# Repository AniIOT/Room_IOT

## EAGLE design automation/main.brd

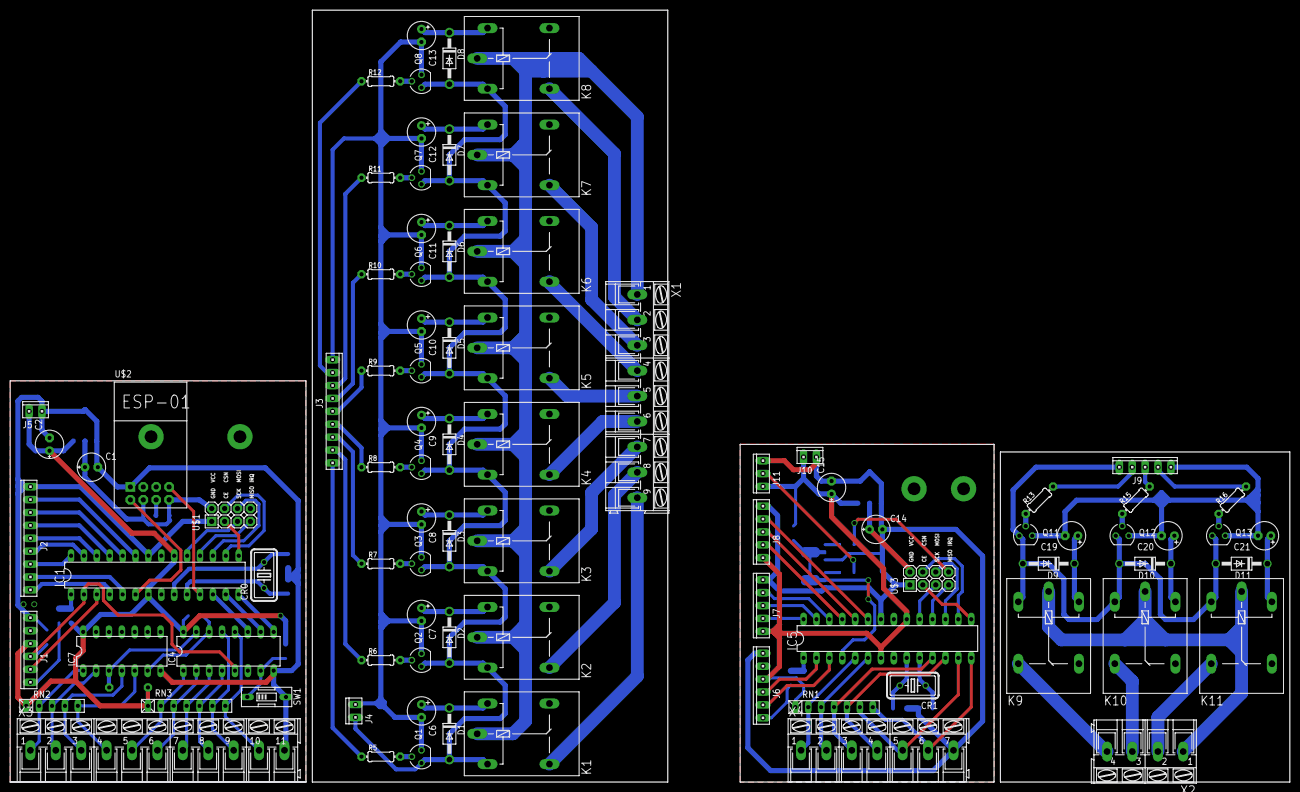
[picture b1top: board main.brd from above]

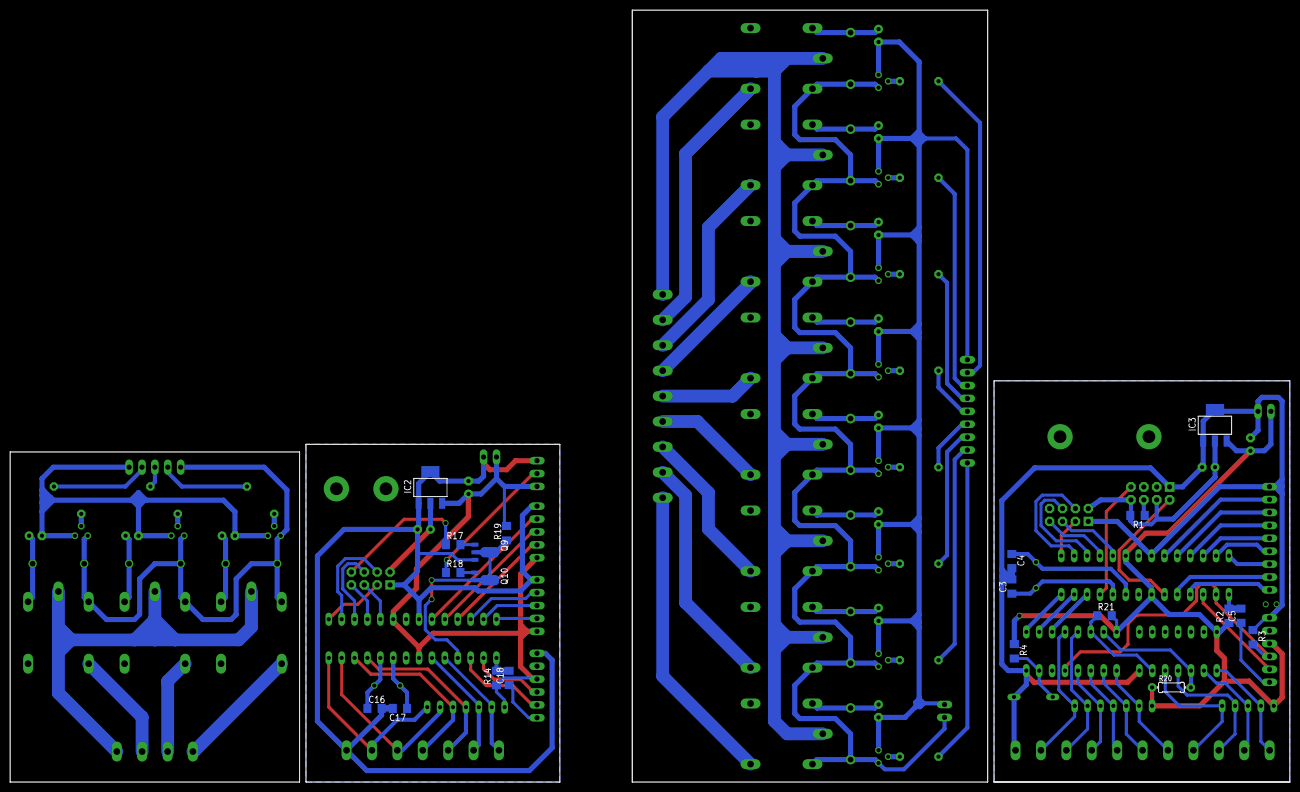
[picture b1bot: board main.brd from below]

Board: 2 copper layers, 252.0 x 152.0 mm, 107 parts (20 on the bottom side), 122 nets.

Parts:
C1, C2: E2,5-6E
C3, C4, C5, C16, C17: C1206
C6, C7, C8, C9, C10, C11, C12, C13, C19, C20, C21: E2,5-6
C14: 100uF; E2,5-6E
C15: 10uF; E2,5-6E
C18: 100nF; C1206
CR0, CR1: 16MHz; HC18U-V
D1, D2, D3, D4, D5, D6, D7, D8, D9, D10, D11: 1N4004; DO41-10
IC1, IC5: ATMEGA328-20P; DIL28-3
IC2, IC3: LM1117IMPX-3.3; SOT223
IC4: 74LS151N; DIL16
IC7: 74LS86N; DIL14
J1, J6: 10X06MTA
J2, J3: 10X09MTA
J4, J5, J10: 10X02MTA
J7, J8, J9: 10X05MTA
J11: 10X03MTA
K1, K2, K3, K4, K5, K6, K7, K8, K9, K10, K11: G5L; G5LE
Q1, Q2, Q3, Q4, Q5, Q6, Q7, Q8, Q11, Q12, Q13: BC547; SOT54A
Q9, Q10: SOT89-BCE
R1, R2, R3, R4, R14, R17, R18, R19, R21: R1206
R5, R6, R7, R8, R9, R10, R11, R12, R13, R15, R16, R20: 0204/7
RN1, RN3: RN-7
RN2: RN-5
SW1: EDG-01
U$1, U$3: NRF24L01+
U$2: ESP01
X1: AK300/9
X2: AK300/4
X3: AK300/11
X4: AK300/7

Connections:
3V3: C1.+, IC3.2, R1.2, U$1.VCC, U$2.CH_PD, U$2.VCC
3V3@2: C14.+, IC2.2, U$3.VCC
5V: C2.+, IC1.7, IC1.20, IC3.3, IC4.16, IC7.14, J1.3, J5.2, R2.1, R4.1, R20.1, R21.2, RN2.1, RN3.1
5V@1: D1.A, D2.A, D3.A, D4.A, D5.A, D6.A, D7.A, D8.A, J4.2, K1.1, K2.1, K3.1, K4.1, K5.1, K6.1, K7.1, K8.1, Q1.C, Q2.C, Q3.C, Q4.C, Q5.C, Q6.C, Q7.C, Q8.C
5V@2: C15.+, IC2.3, IC5.7, IC5.20, J6.3, J7.5, J8.5, J10.2, J11.3, R14.1, R19.2, RN1.1
5V@2R: D9.A, D10.A, D11.A, J9.5, K9.1, K10.1, K11.1, Q11.C, Q12.C, Q13.C
CE: IC1.15, U$1.CE
CE2: IC5.15, U$3.CE
CR1: C4.1, CR0.2, IC1.9
CR2: C3.1, CR0.1, IC1.10
CR3: C16.1, CR1.1, IC5.10
CR4: C17.1, CR1.2, IC5.9
CSN: IC1.16, U$1.CSN
CSN2: IC5.16, U$3.CSN
DTR: C5.1, J1.6
DTR2: C18.1, J6.6
ERST: R1.1, U$2.RST
FSW1: IC7.1, RN2.2, X3.1
FSW2: IC7.2, RN2.3, X3.2
GND: C1.-, C2.-, C3.2, C4.2, IC1.22, IC3.1, IC3.TAB, IC4.8, IC7.7, J1.1, J2.1, J5.1, R3.1, SW1.2, U$1.GND, U$2.GND, X3.11
GND@1: C6.-, C7.-, C8.-, C9.-, C10.-, C11.-, C12.-, C13.-, J3.9, J4.1, Q1.E, Q2.E, Q3.E, Q4.E, Q5.E, Q6.E, Q7.E, Q8.E
GND@2: C14.-, C15.-, C16.2, C17.2, IC2.1, IC2.TAB, IC5.22, J6.1, J7.1, J8.1, J10.1, J11.1, Q9.E, Q10.E, U$3.GND, X4.7
GND@2R: C19.-, C20.-, C21.-, J9.1, Q11.E, Q12.E, Q13.E
IRQ: R17.1, U$3.IRQ
IRQ+PIR: IC5.4, Q9.C, Q10.C, R19.1
LIVE: K1.P, K2.P, K3.P, K4.P, K5.P, K6.P, K7.P, K8.P, X1.1
MEN: IC4.7, R4.2, SW1.1
MISO: IC1.18, U$1.MISO
MISO2: IC5.18, U$3.MISO
MOSI: IC1.17, U$1.MOSI
MOSI2: IC5.17, U$3.MOSI
MRST: C5.2, IC1.1, R2.2
MRST1: C18.2, IC5.1, R14.2
unnamed: K9.P, K10.P, K11.P, X2.1
unnamed: Q1.B, R5.2
unnamed: Q2.B, R6.2
unnamed: Q3.B, R7.2
unnamed: Q4.B, R8.2
unnamed: Q5.B, R9.2
unnamed: Q6.B, R10.2
unnamed: Q7.B, R11.2
unnamed: Q8.B, R12.2
unnamed: J3.1, R5.1
unnamed: J3.8, R12.1
unnamed: J3.7, R11.1
unnamed: J3.6, R10.1
unnamed: J3.5, R9.1
unnamed: J3.4, R8.1
unnamed: J3.3, R7.1
unnamed: J3.2, R6.1
unnamed: K1.S, X1.9
unnamed: K8.S, X1.2
unnamed: K7.S, X1.3
unnamed: K6.S, X1.4
unnamed: K5.S, X1.5
unnamed: K4.S, X1.6
unnamed: K3.S, X1.7
unnamed: K2.S, X1.8
unnamed: C19.+, D9.C, K9.2
unnamed: C7.+, D2.C, K2.2
unnamed: C8.+, D3.C, K3.2
unnamed: C9.+, D4.C, K4.2
unnamed: C10.+, D5.C, K5.2
unnamed: C11.+, D6.C, K6.2
unnamed: C12.+, D7.C, K7.2
unnamed: C13.+, D8.C, K8.2
unnamed: C6.+, D1.C, K1.2
unnamed: K10.S, X2.3
unnamed: C20.+, D10.C, K10.2
unnamed: K9.S, X2.4
unnamed: C21.+, D11.C, K11.2
unnamed: K11.S, X2.2
unnamed: Q11.B, R13.1
unnamed: Q13.B, R16.1
unnamed: Q12.B, R15.1
unnamed: J9.3, R15.2
unnamed: J9.4, R13.2
unnamed: J9.2, R16.2
unnamed: Q9.B, R17.2
unnamed: Q10.B, R18.2
PIR: J11.2, R18.1
PRX: IC1.3, J1.5
PRX2: IC5.3, J6.5
PTX2: IC5.2, J6.4
PTX+SWS: IC1.2, IC4.5, J1.4, R3.2
RELAY1: IC1.4, J2.9
RELAY2: IC1.5, J2.8
RELAY3: IC1.28, J2.7
RELAY4: IC1.27, J2.6
RELAY5: IC1.26, J2.5
RELAY6: IC1.25, J2.4
RELAY7: IC1.24, J2.3
RELAY8: IC1.23, J2.2
RELAY21: IC5.28, J7.4
RELAY22: IC5.27, J7.3
RELAY23: IC5.26, J7.2
RELAY24: IC5.25, J8.4
RELAY25: IC5.24, J8.3
RELAY26: IC5.23, J8.2
RX: IC1.11, U$2.RX
S1: IC1.12, IC4.11
S2: IC1.13, IC4.10
S3: IC1.14, IC4.9
S21: IC5.5, RN1.2, X4.1
S22: IC5.6, RN1.3, X4.2
S23: IC5.11, RN1.4, X4.3
S24: IC5.12, RN1.5, X4.4
S25: IC5.13, RN1.6, X4.5
S26: IC5.14, RN1.7, X4.6
SCK: IC1.19, U$1.SCK
SCK2: IC5.19, U$3.SCK
SW1: IC4.15, IC7.3, R20.2
SW2: IC4.14, IC7.6, R21.1
SW3: IC4.1, RN3.2, X3.5
SW4: IC4.2, RN3.3, X3.6
SW5: IC4.3, RN3.4, X3.7
SW6: IC4.4, RN3.5, X3.8
SW7: IC4.13, RN3.6, X3.9
SW8: IC4.12, RN3.7, X3.10
TSW1: IC7.4, RN2.4, X3.3
TSW2: IC7.5, RN2.5, X3.4
TX: IC1.6, U$2.TX

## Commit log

2019-09-12 Deposited all previous files
2019-09-12 Added de-bouncing for switches and a temporary function call in the wifi_comm state in main state machine
2019-09-13 added reference modbus and uart files
2019-09-13 corrected a few issues
2019-09-13 made changes to debouncing in gpio.ino, created files for node01 and added the new structure and debouncing of switches to gpio.ino
2019-09-15 Changed library for software serial, now using neoswserial which now has an isr to handle reception
2019-09-15 Created files and structure for esp8266 MODBUS_Rx.ino & MODBUS_Tx.ino: added and tested interrupt based serial comm
2019-09-15 changed folder name of esp_mqtt to esp_main
2019-09-20 lot of changes in communication.
2019-09-20 added esp flash download tools
2019-09-25 added callback funtion in esp_main which has tremendously reduced number of dropped packages.
2019-09-25 flash_download_tool
2019-09-26 added send data function call to callback function
2019-09-27 completed uart communication and mqtt callback
2019-09-27 no idea
2019-09-28 lotsa stuff
2019-09-29 added wtchdog and rf comm
2019-09-30 SP college ppt
2019-10-14 added state in main state machine for storing data in eeprom
2019-10-15 re-upload
2019-10-27 removed the separate folder for room
2019-11-07 header name changed to node02
2019-11-15 1. In esp_main.ino added software watchdog 2. In gpio.ino interchanged pins of extra switch and w4 as the cause of wrong switching was a hardware short 3. In node01.ino commented wifi_comm() to avoid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
2020-04-08 swapped switches
2020-04-11 Created V3 of code and added esp state machine
2020-04-16 1. Removed all .h files except for node00.h 2. Wrote code for MQTT connect request
2020-04-18 1. code for subscribe 2. code for ping 3. completed mqtt state machine 4. added call of esp state machine from mqtt state machine
2020-04-19 Restructuring of Repository
2020-04-19 refactoring of code to make connectToServer and subscribe functions generic with added function parameters
2020-04-19 Added esp tools
2020-04-24 Subscription and data acquisition from all 25 topics completed
2020-04-24 Added switch buffer and logic
2020-04-26 1. Added reconnect logic 2. Cleaned up code 3. Added logic fro checking connection to safe time
2020-04-26 1. Added Timed function calling (a rudimentary non-preemptive scheduler) 2. Made file and function for switches
2020-04-26 added else condition for connect and subscribe states in mqtt state-machine
2020-04-28 1. Added timer based function calling
2020-04-29 Added logic for taking acknowledgment for every subscription request
2020-04-30 1. Added macros for relays, switches and NRF24L01 2. Added pin configuration for relays and switches 3. Added code for de-bouncing and reading 2 switches
2020-05-03 1. Added nrf24l01 datasheet
2020-05-03 1. added ascii table
2020-05-25 Created folder for remote
